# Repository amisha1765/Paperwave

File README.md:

# Paperwave

## Relevant Datasheets
TFT: https://cdn-shop.adafruit.com/datasheets/ILI9341.pdf

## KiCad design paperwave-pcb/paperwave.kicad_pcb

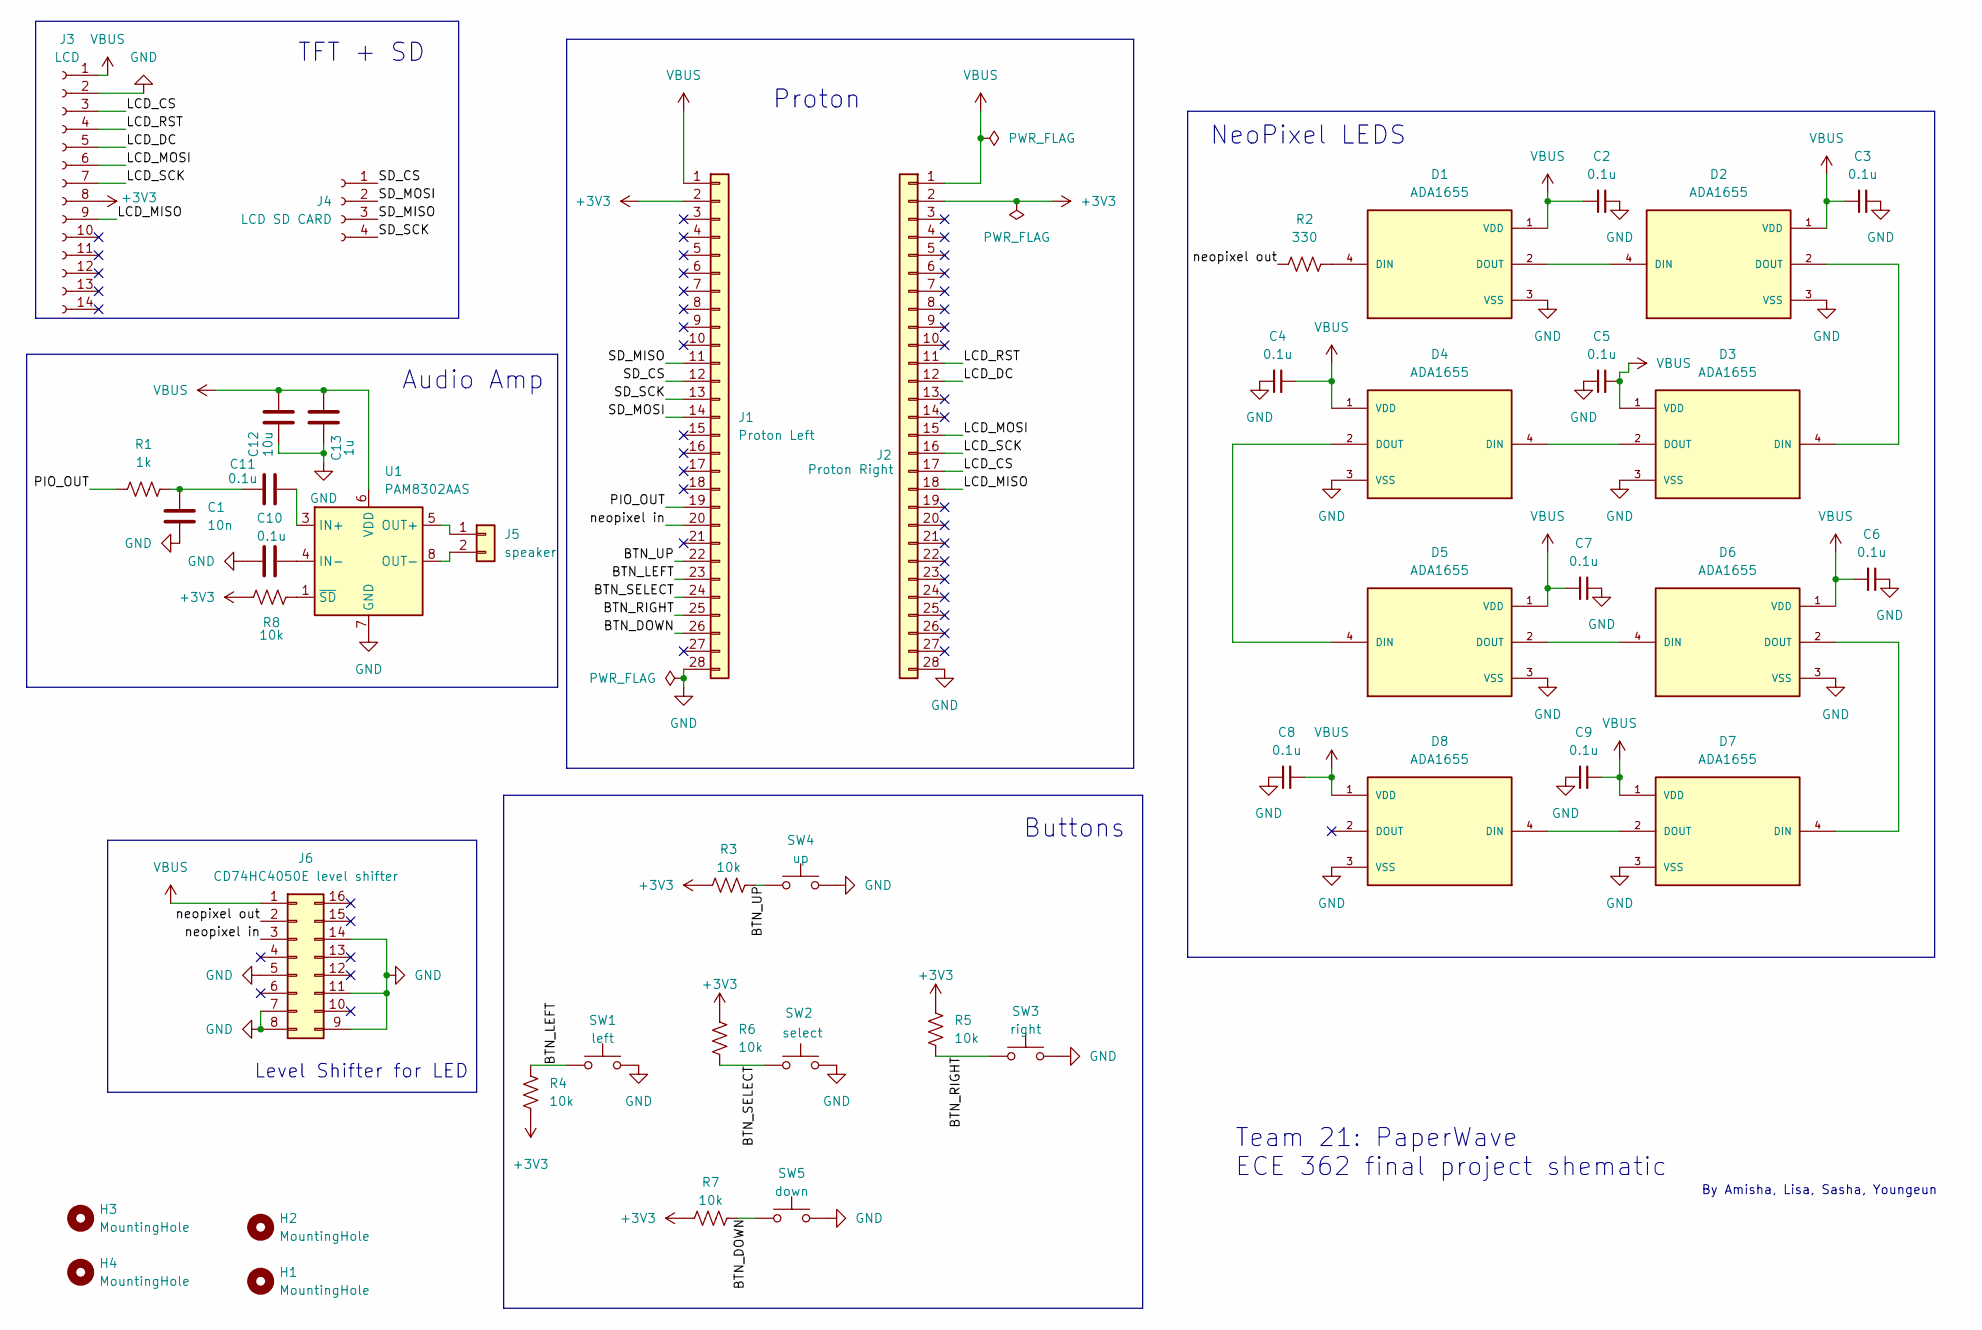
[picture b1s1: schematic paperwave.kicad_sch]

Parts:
C1: 10n; C_Disc_D5.0mm_W2.5mm_P2.50mm
C2, C3, C4, C5, C6, C7, C8, C9, C10, C11: 0.1u; C_Disc_D5.0mm_W2.5mm_P2.50mm
C12: 10u; C_Disc_D5.0mm_W2.5mm_P2.50mm
C13: 1u; C_Disc_D5.0mm_W2.5mm_P2.50mm
D1, D2, D3, D4, D5, D6, D7, D8: ADA1655; LED_ADA1655; MPN ADA1655
H1, H2, H3, H4: MountingHole; MountingHole_3.5mm
J1: Proton Left; PinSocket_1x28_P2.54mm_Vertical
J2: Proton Right; PinSocket_1x28_P2.54mm_Vertical
J3: LCD; PinHeader_1x14_P2.54mm_Vertical
J4: LCD SD CARD; PinHeader_1x04_P2.54mm_Vertical
J5: speaker; PinSocket_1x02_P2.54mm_Vertical
J6: CD74HC4050E level shifter; DIP-16_W7.62mm
R1: 1k; R_Axial_DIN0207_L6.3mm_D2.5mm_P7.62mm_Horizontal
R2: 330; R_Axial_DIN0207_L6.3mm_D2.5mm_P7.62mm_Horizontal
R3, R4, R5, R6, R7, R8: 10k; R_Axial_DIN0207_L6.3mm_D2.5mm_P7.62mm_Horizontal
SW1: left; SW_PUSH_6mm
SW2: select; SW_PUSH_6mm
SW3: right; SW_PUSH_6mm
SW4: up; SW_PUSH_6mm
SW5: down; SW_PUSH_6mm
U1: PAM8302AAS; DFN-8-1EP_2x2mm_P0.5mm_EP0.86x1.55mm

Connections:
+3V3: J1.2, J2.2, J3.8, R3.1, R4.1, R5.1, R6.1, R7.1, R8.2
/BTN_DOWN: J1.26, R7.2, SW5.1
/BTN_LEFT: J1.23, R4.2, SW1.1
/BTN_RIGHT: J1.25, R5.2, SW3.1
/BTN_SELECT: J1.24, R6.2, SW2.1
/BTN_UP: J1.22, R3.2, SW4.1
/LCD_CS: J2.17, J3.3
/LCD_DC: J2.12, J3.5
/LCD_MISO: J2.18, J3.9
/LCD_MOSI: J2.15, J3.6
/LCD_RST: J2.11, J3.4
/LCD_SCK: J2.16, J3.7
/PIO_OUT: J1.19, R1.1
/SD_CS: J1.12, J4.1
/SD_MISO: J1.11, J4.3
/SD_MOSI: J1.14, J4.2
/SD_SCK: J1.13, J4.4
/neopixel in: J1.20, J6.3
/neopixel out: J6.2, R2.1
GND: C1.2, C2.2, C3.2, C4.2, C5.2, C6.2, C7.2, C8.2, C9.2, C10.1, C12.1, C13.1, D1.3 (VSS), D2.3 (VSS), D3.3 (VSS), D4.3 (VSS), D5.3 (VSS), D6.3 (VSS), D7.3 (VSS), D8.3 (VSS), J1.28, J2.28, J3.2, J6.5, J6.7, J6.8, J6.9, J6.11, J6.14, SW1.2, SW2.2, SW3.2, SW4.2, SW5.2, U1.7 (GND)
unnamed: C1.1, C11.1, R1.2
unnamed: D1.4 (DIN), R2.2
unnamed: D1.2 (DOUT), D2.4 (DIN)
unnamed: D2.2 (DOUT), D3.4 (DIN)
unnamed: D3.2 (DOUT), D4.4 (DIN)
unnamed: D4.2 (DOUT), D5.4 (DIN)
unnamed: D5.2 (DOUT), D6.4 (DIN)
unnamed: D6.2 (DOUT), D7.4 (DIN)
unnamed: D7.2 (DOUT), D8.4 (DIN)
unnamed: J5.1, U1.5 (OUT+)
unnamed: J5.2, U1.8 (OUT-)
unnamed: C11.2, U1.3 (IN+)
unnamed: C10.2, U1.4 (IN-)
unnamed: R8.1, U1.1 (~SD)
VBUS: C2.1, C3.1, C4.1, C5.1, C6.1, C7.1, C8.1, C9.1, C12.2, C13.2, D1.1 (VDD), D2.1 (VDD), D3.1 (VDD), D4.1 (VDD), D5.1 (VDD), D6.1 (VDD), D7.1 (VDD), D8.1 (VDD), J1.1, J2.1, J3.1, J6.1, U1.6 (VDD)

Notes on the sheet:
Proton
Buttons
Level Shifter for LED
NeoPixel LEDS
By Amisha, Lisa, Sasha, Youngeun
TFT + SD
Audio Amp
Team 21: PaperWave ECE 362 final project shematic

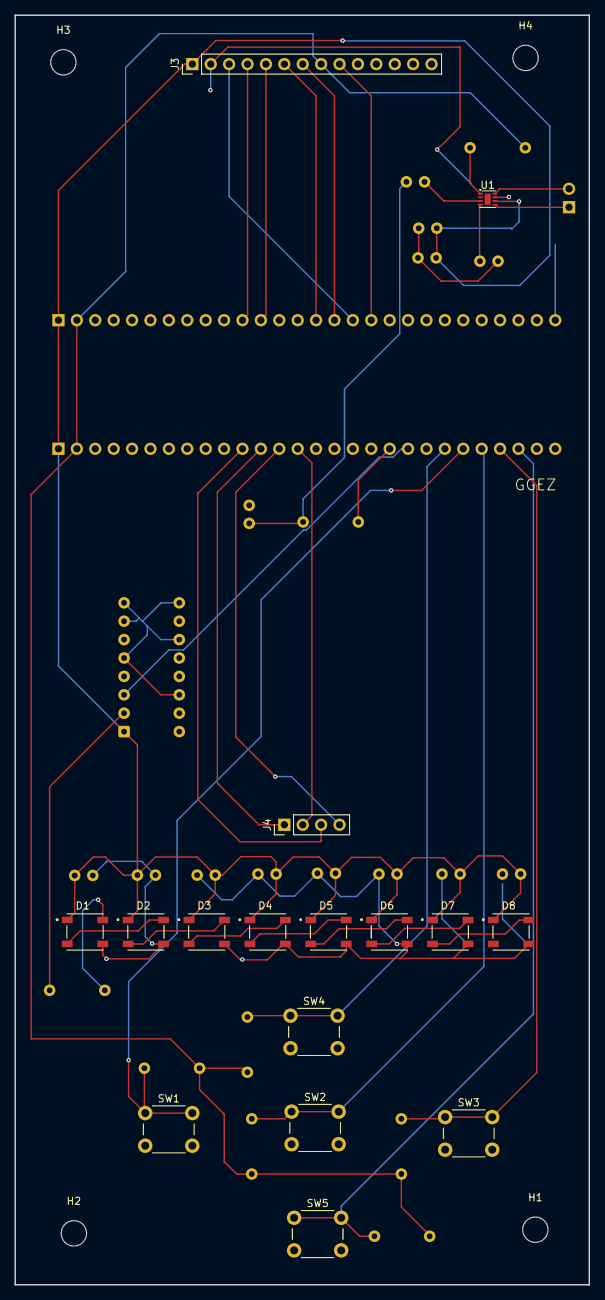
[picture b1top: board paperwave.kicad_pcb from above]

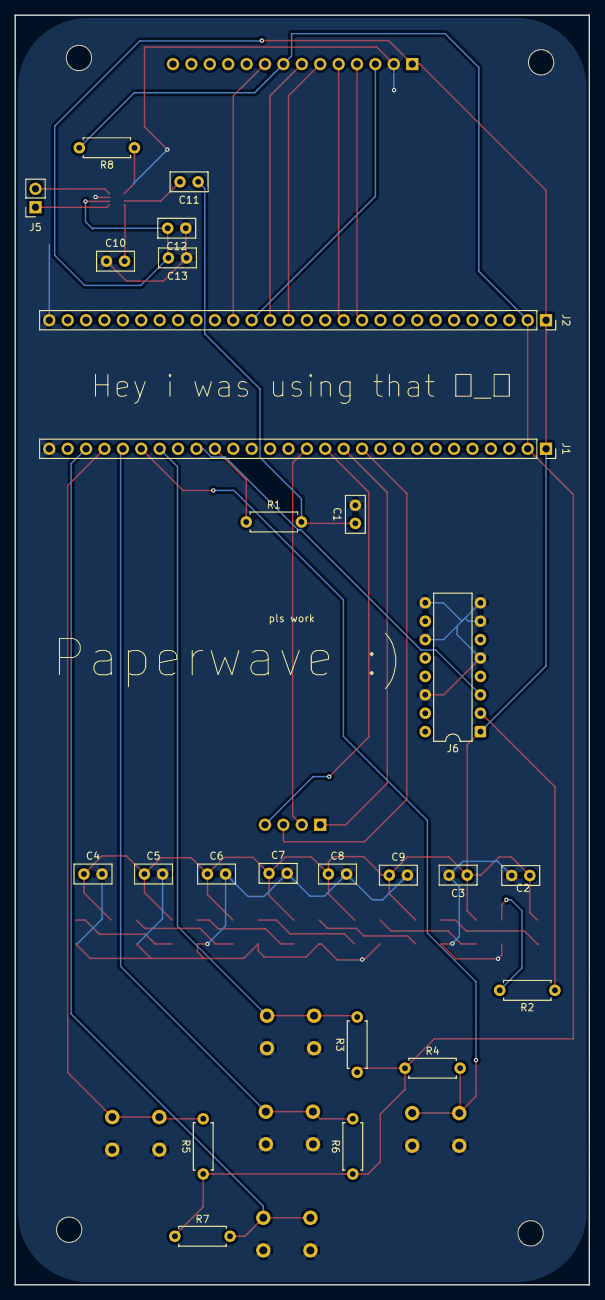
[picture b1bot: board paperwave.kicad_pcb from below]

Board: 2 copper layers, 79.2 x 175.2 mm, 45 parts (25 on the bottom side), 35 nets.

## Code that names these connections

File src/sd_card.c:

//initializations
#include "sd_card.h"
#include "pico/stdlib.h"
#include "hardware/spi.h"
#include "hardware/gpio.h"

//define variables
#define SD_SPI spi1
#define SD_CS_PIN   9
#define SD_MISO_PIN 8
#define SD_MOSI_PIN 11
#define SD_SCK_PIN  10

static bool sd_check_cmd8(void);

// SPI initialization.
static void sd_spi_init(void){
    //400kHZ for now, can increase later this is for testing purposes
    spi_init(SD_SPI, 400 * 1000);
    spi_set_format(SD_SPI, 8, SPI_CPOL_0, SPI_CPHA_0, SPI_MSB_FIRST);

    // Configure SPI GPIO pins
    gpio_set_function(SD_MISO_PIN, GPIO_FUNC_SPI);
    gpio_set_function(SD_MOSI_PIN, GPIO_FUNC_SPI);
    gpio_set_function(SD_SCK_PIN, GPIO_FUNC_SPI);

    // Configure chip select as a normal GPIO output
    gpio_init(SD_CS_PIN);
    gpio_set_dir(SD_CS_PIN, GPIO_OUT);
    gpio_put(SD_CS_PIN, 1);
}

// Send one byte and receive one byte
static uint8_t sd_spi_transfer(uint8_t data){
    uint8_t received;
    spi_write_read_blocking(SD_SPI, &data, &received, 1);
    return received;
}

// Receive multiple bytes
static void sd_spi_receive(uint8_t *buffer, uint32_t length){
    spi_read_blocking(SD_SPI, 0xFF, buffer, length);
}

//chip select functions
static void sd_select(void){
    //when CS signal LOW, communicate with SD card
    gpio_put(SD_CS_PIN, 0);
}

static void sd_deselect(void){
    //when CS signal HIGH, stop selecting SD card
    gpio_put(SD_CS_PIN, 1);
    // Send extra clock cycles while deselected
    sd_spi_transfer(0xFF);
}

//SD card intitalization
static uint8_t sd_send_command(uint8_t command, uint32_t argument, uint8_t crc){
    uint8_t response;
    sd_select(); // Select the SD card
    sd_spi_transfer(0xFF); // Give the card an extra clock cycle
    sd_spi_transfer(0x40 | command); // Send command packet
    // Use this bc the starting has 01 start bits and 6 bit command number, the OR basically adds the starting bits 

    // Send 32-bit argument, one byte at a time
    sd_spi_transfer((argument >> 24) & 0xFF);
    sd_spi_transfer((argument >> 16) & 0xFF);
    sd_spi_transfer((argument >> 8) & 0xFF);
    sd_spi_transfer(argument & 0xFF);

    // Send CRC
    sd_spi_transfer(crc); //Fixed at the end of CMD0

    // Wait for the card's response
    for (int i = 0; i < 10; i++)
    {
        response = sd_spi_transfer(0xFF);

        // Bit 7 becomes zero when an R1 response arrives
        if ((response & 0x80) == 0) {return response;}
    }
    // No valid response received
    return 0xFF;
}

// Initialize the SD card
bool sd_card_init(void){
    sd_spi_init();

    // Send at least 74 clock cycles with CS HIGH
    for (int i = 0; i < 10; i++) {sd_spi_transfer(0xFF);}

    // CMD0: Reset SD card
    uint8_t response = sd_send_command(0, 0, 0x95);
    sd_deselect();
    if (response != 0x01) {return false;}

    // CMD8: Check SD version and voltage
    if (!sd_check_cmd8()) {return false;}
    return true;
}

//implement CMD 8
static bool sd_check_cmd8(void) {
    // Send CMD8 with voltage and check-pattern argument
    uint8_t response = sd_send_command(8, 0x000001AA, 0x87);

    // CMD8 should return 0x01 for an SD v2 card in idle state
    if (response != 0x01) {
        sd_deselect();
        return false;
    }

    // CMD8 returns four additional bytes (R7 response)
    uint8_t r7[4];

    for (int i = 0; i < 4; i++) {
        r7[i] = sd_spi_transfer(0xFF);
    }
    sd_deselect();

    // Check that the card accepted the voltage and check pattern
    if (r7[2] != 0x01 || r7[3] != 0xAA) {return false;}
    return true;
}
